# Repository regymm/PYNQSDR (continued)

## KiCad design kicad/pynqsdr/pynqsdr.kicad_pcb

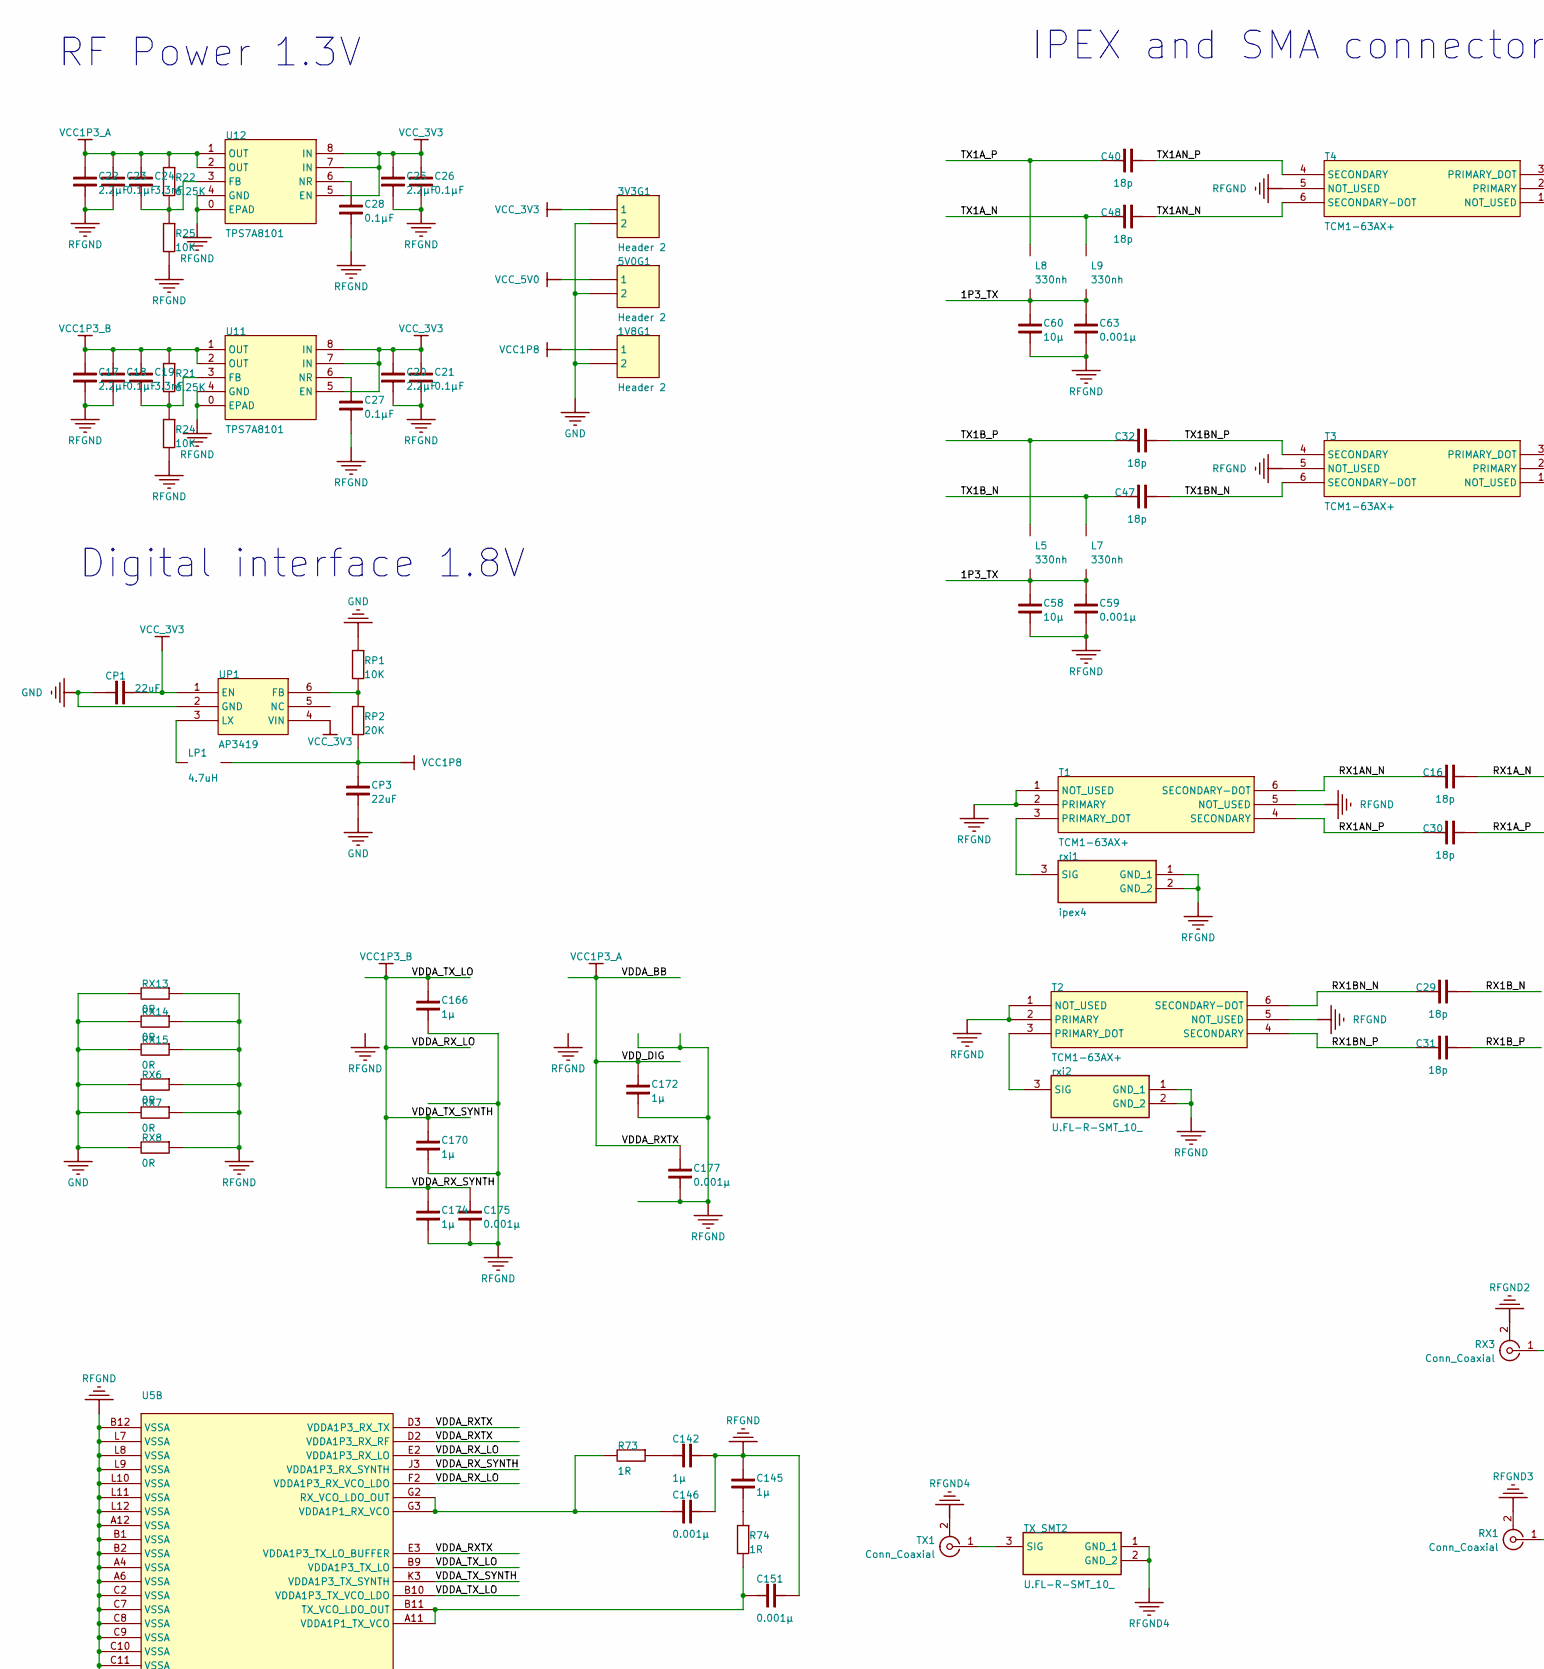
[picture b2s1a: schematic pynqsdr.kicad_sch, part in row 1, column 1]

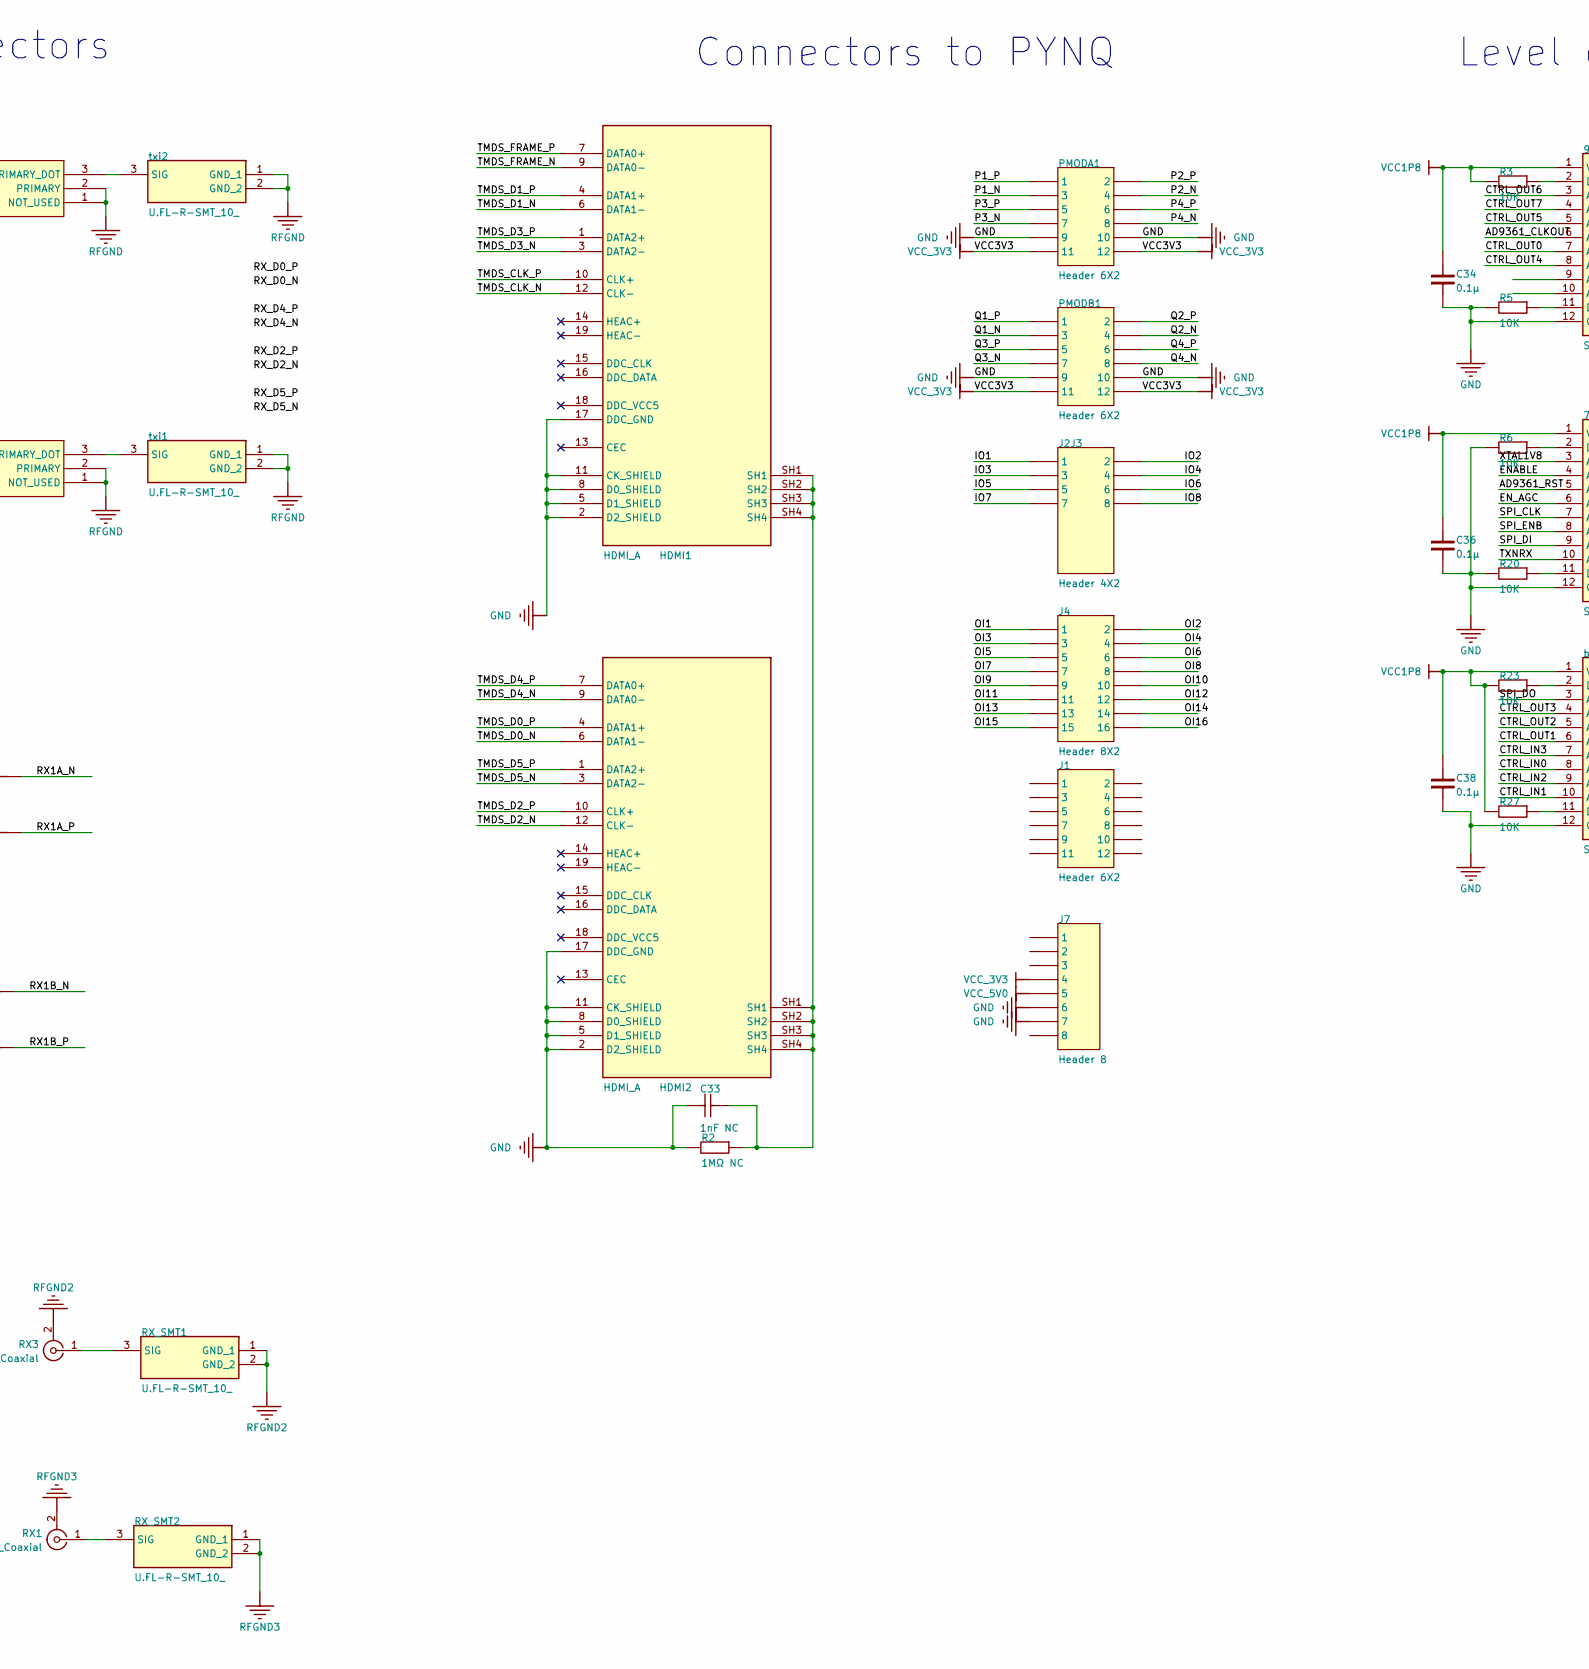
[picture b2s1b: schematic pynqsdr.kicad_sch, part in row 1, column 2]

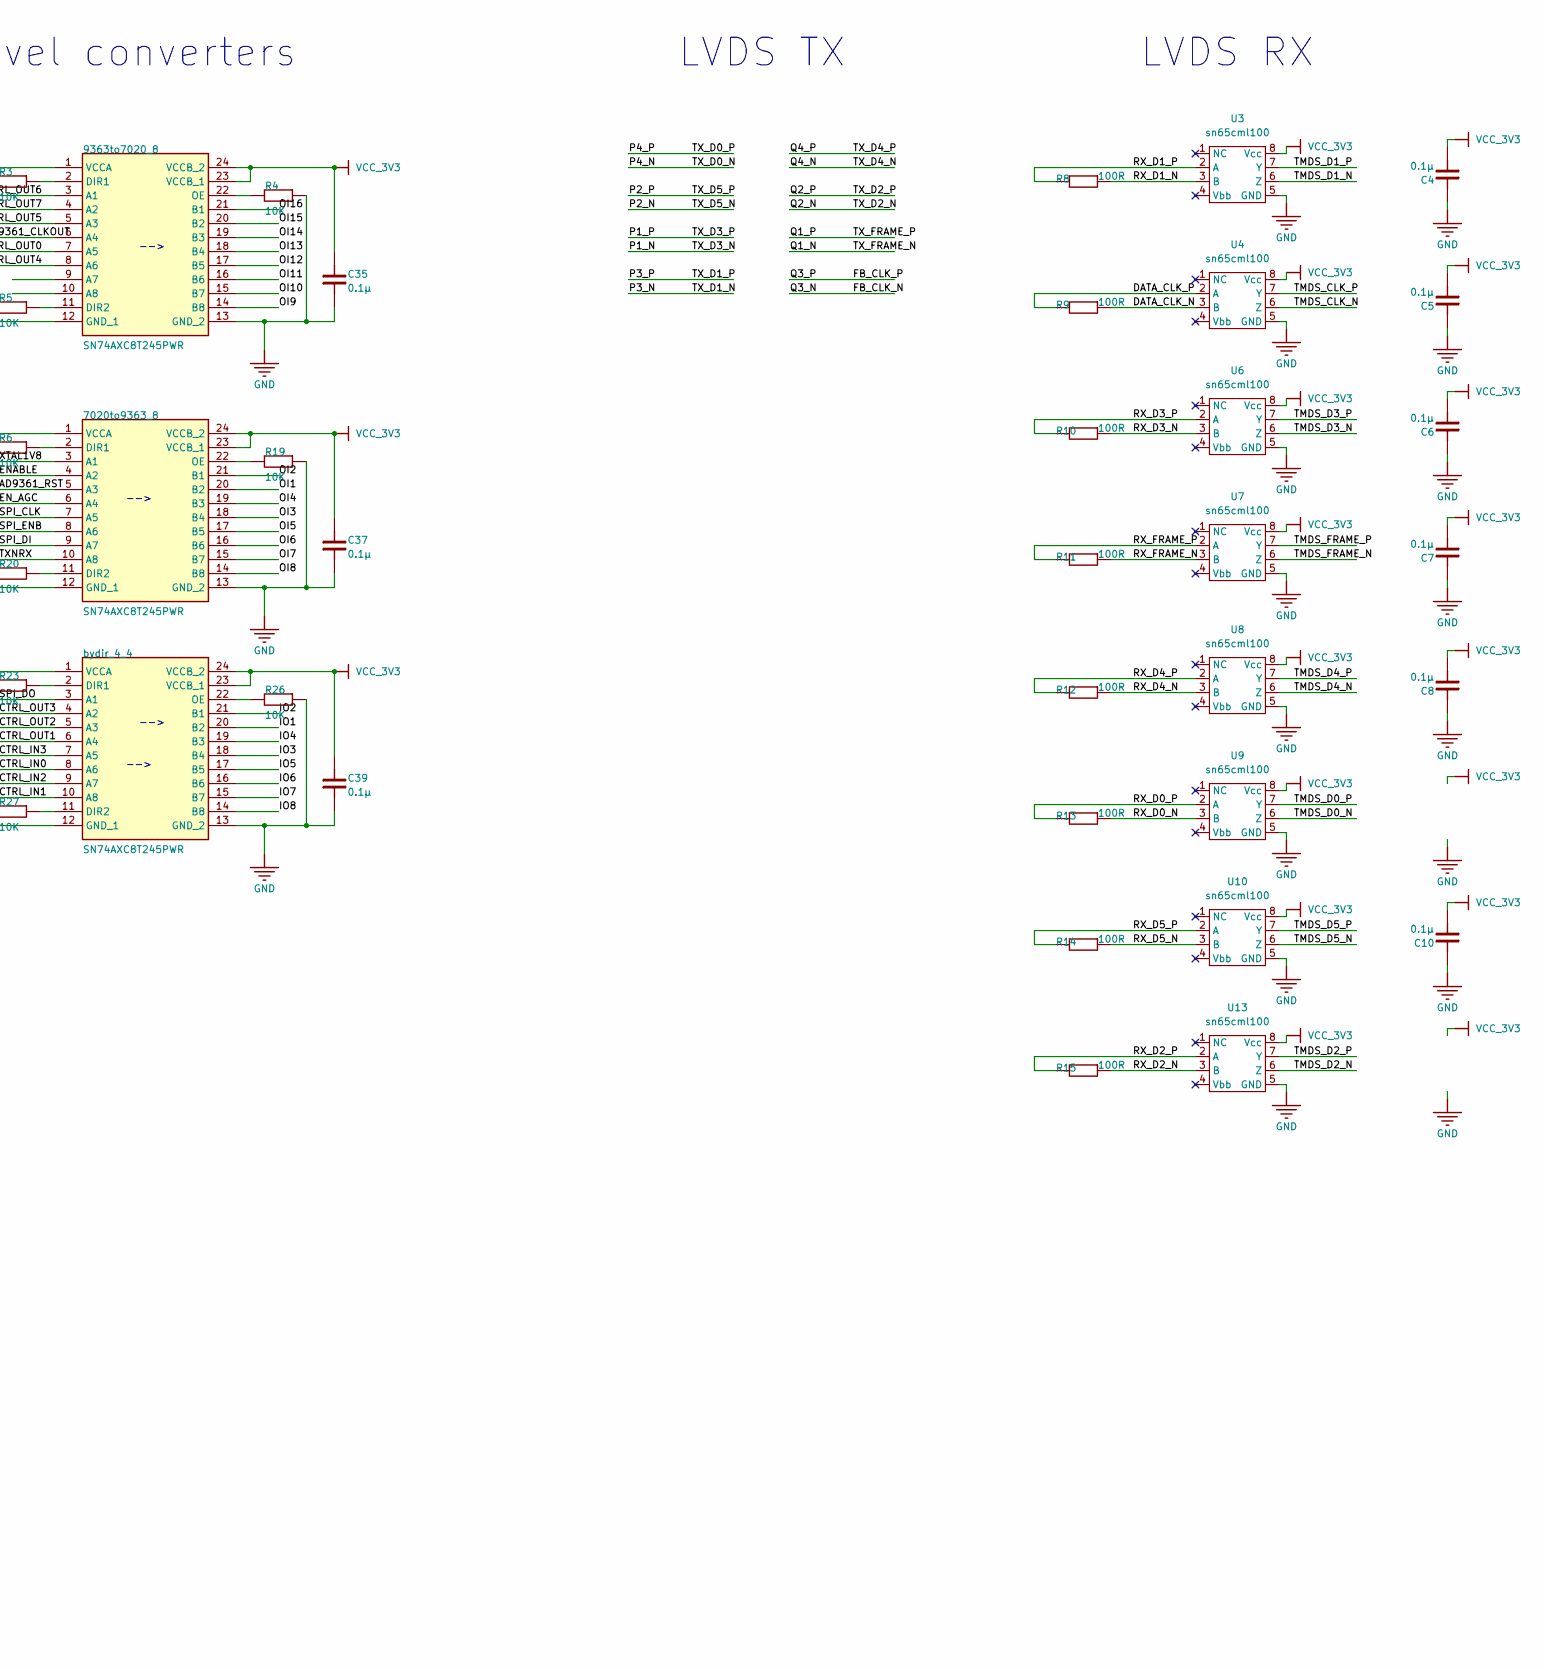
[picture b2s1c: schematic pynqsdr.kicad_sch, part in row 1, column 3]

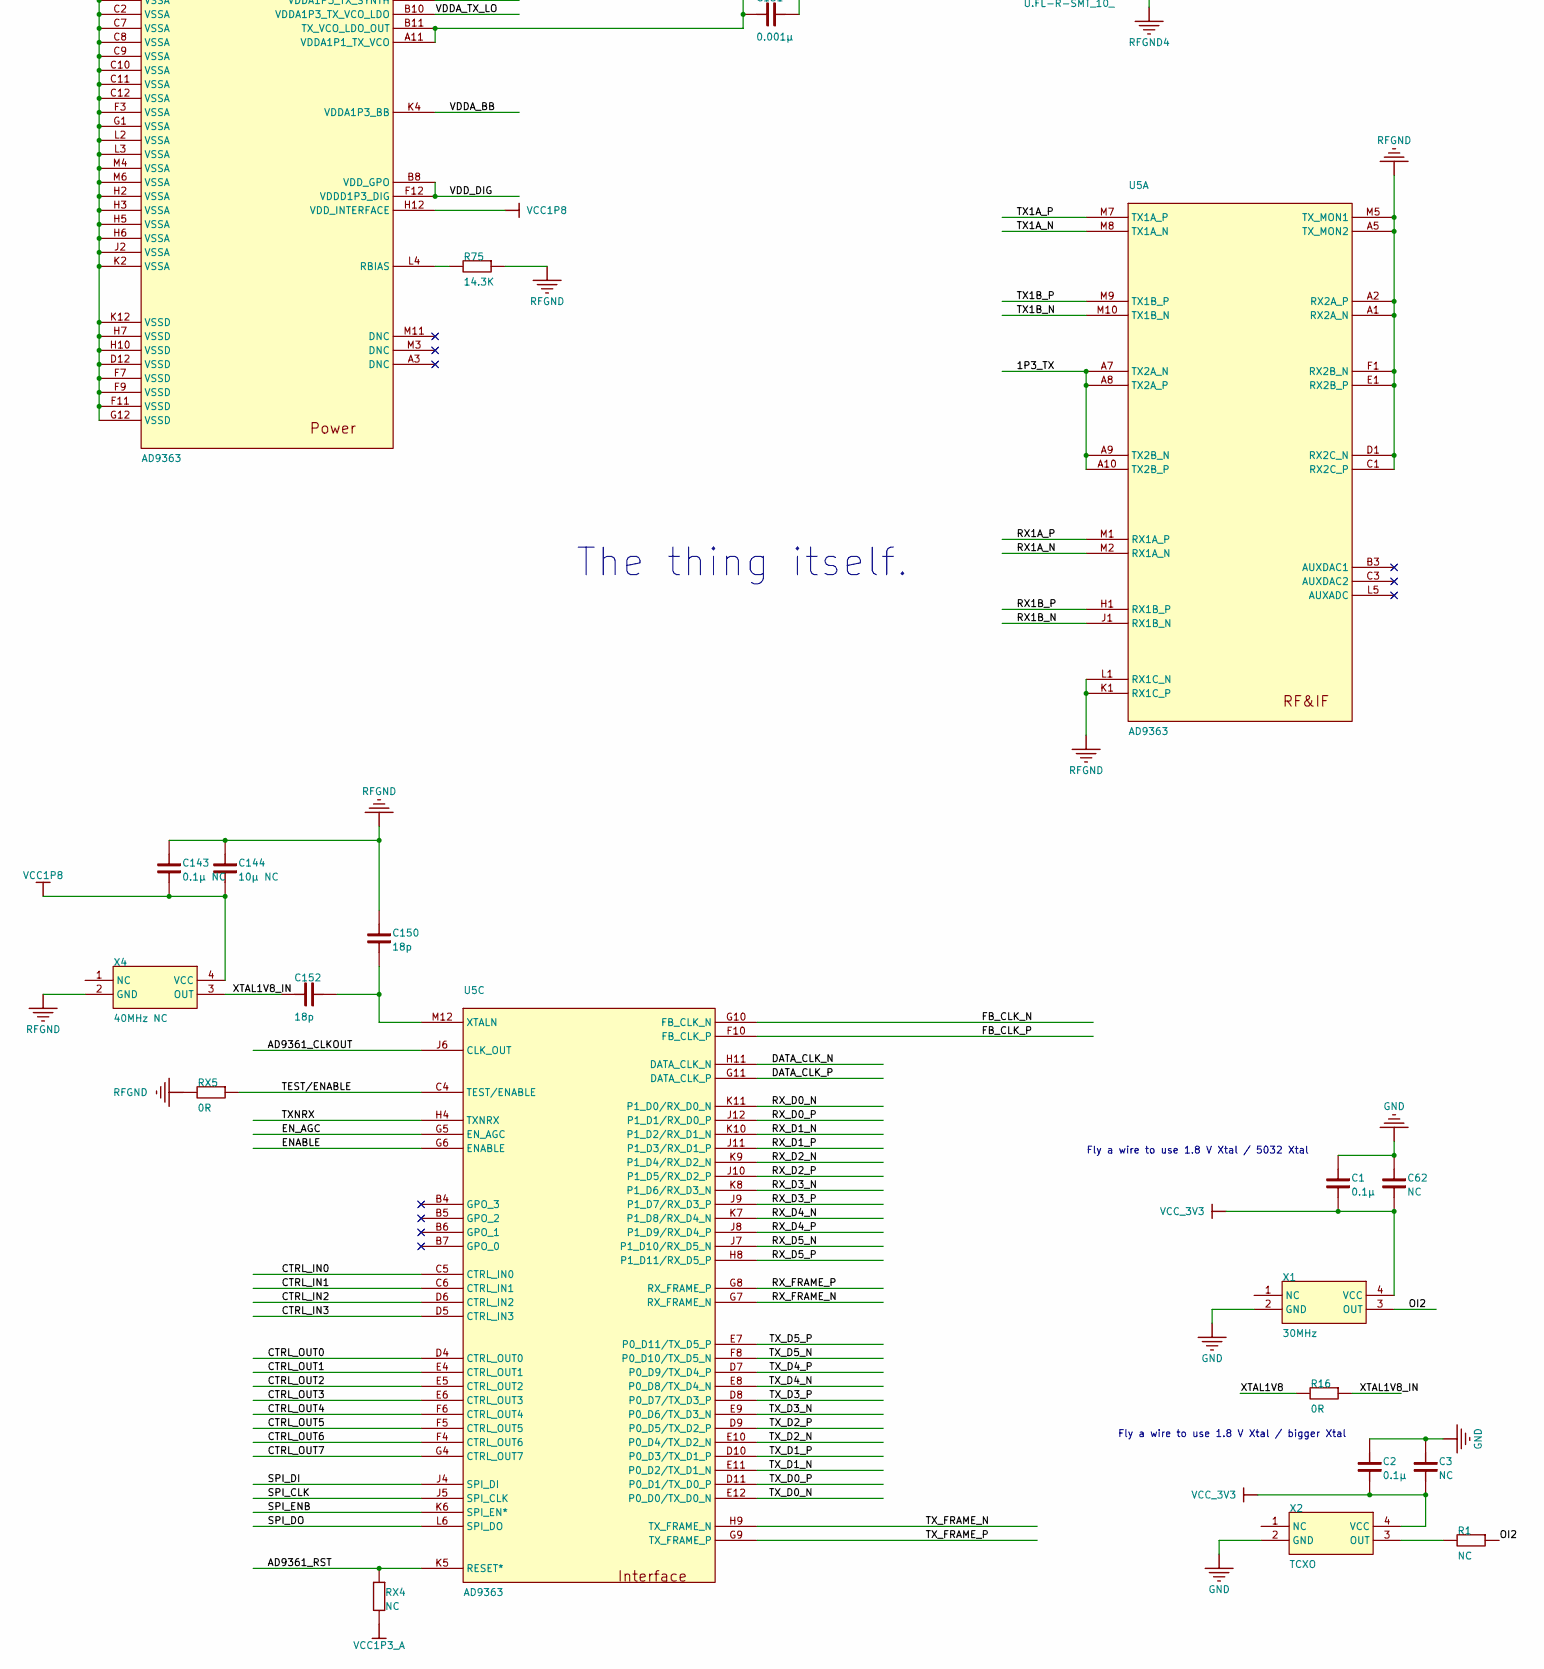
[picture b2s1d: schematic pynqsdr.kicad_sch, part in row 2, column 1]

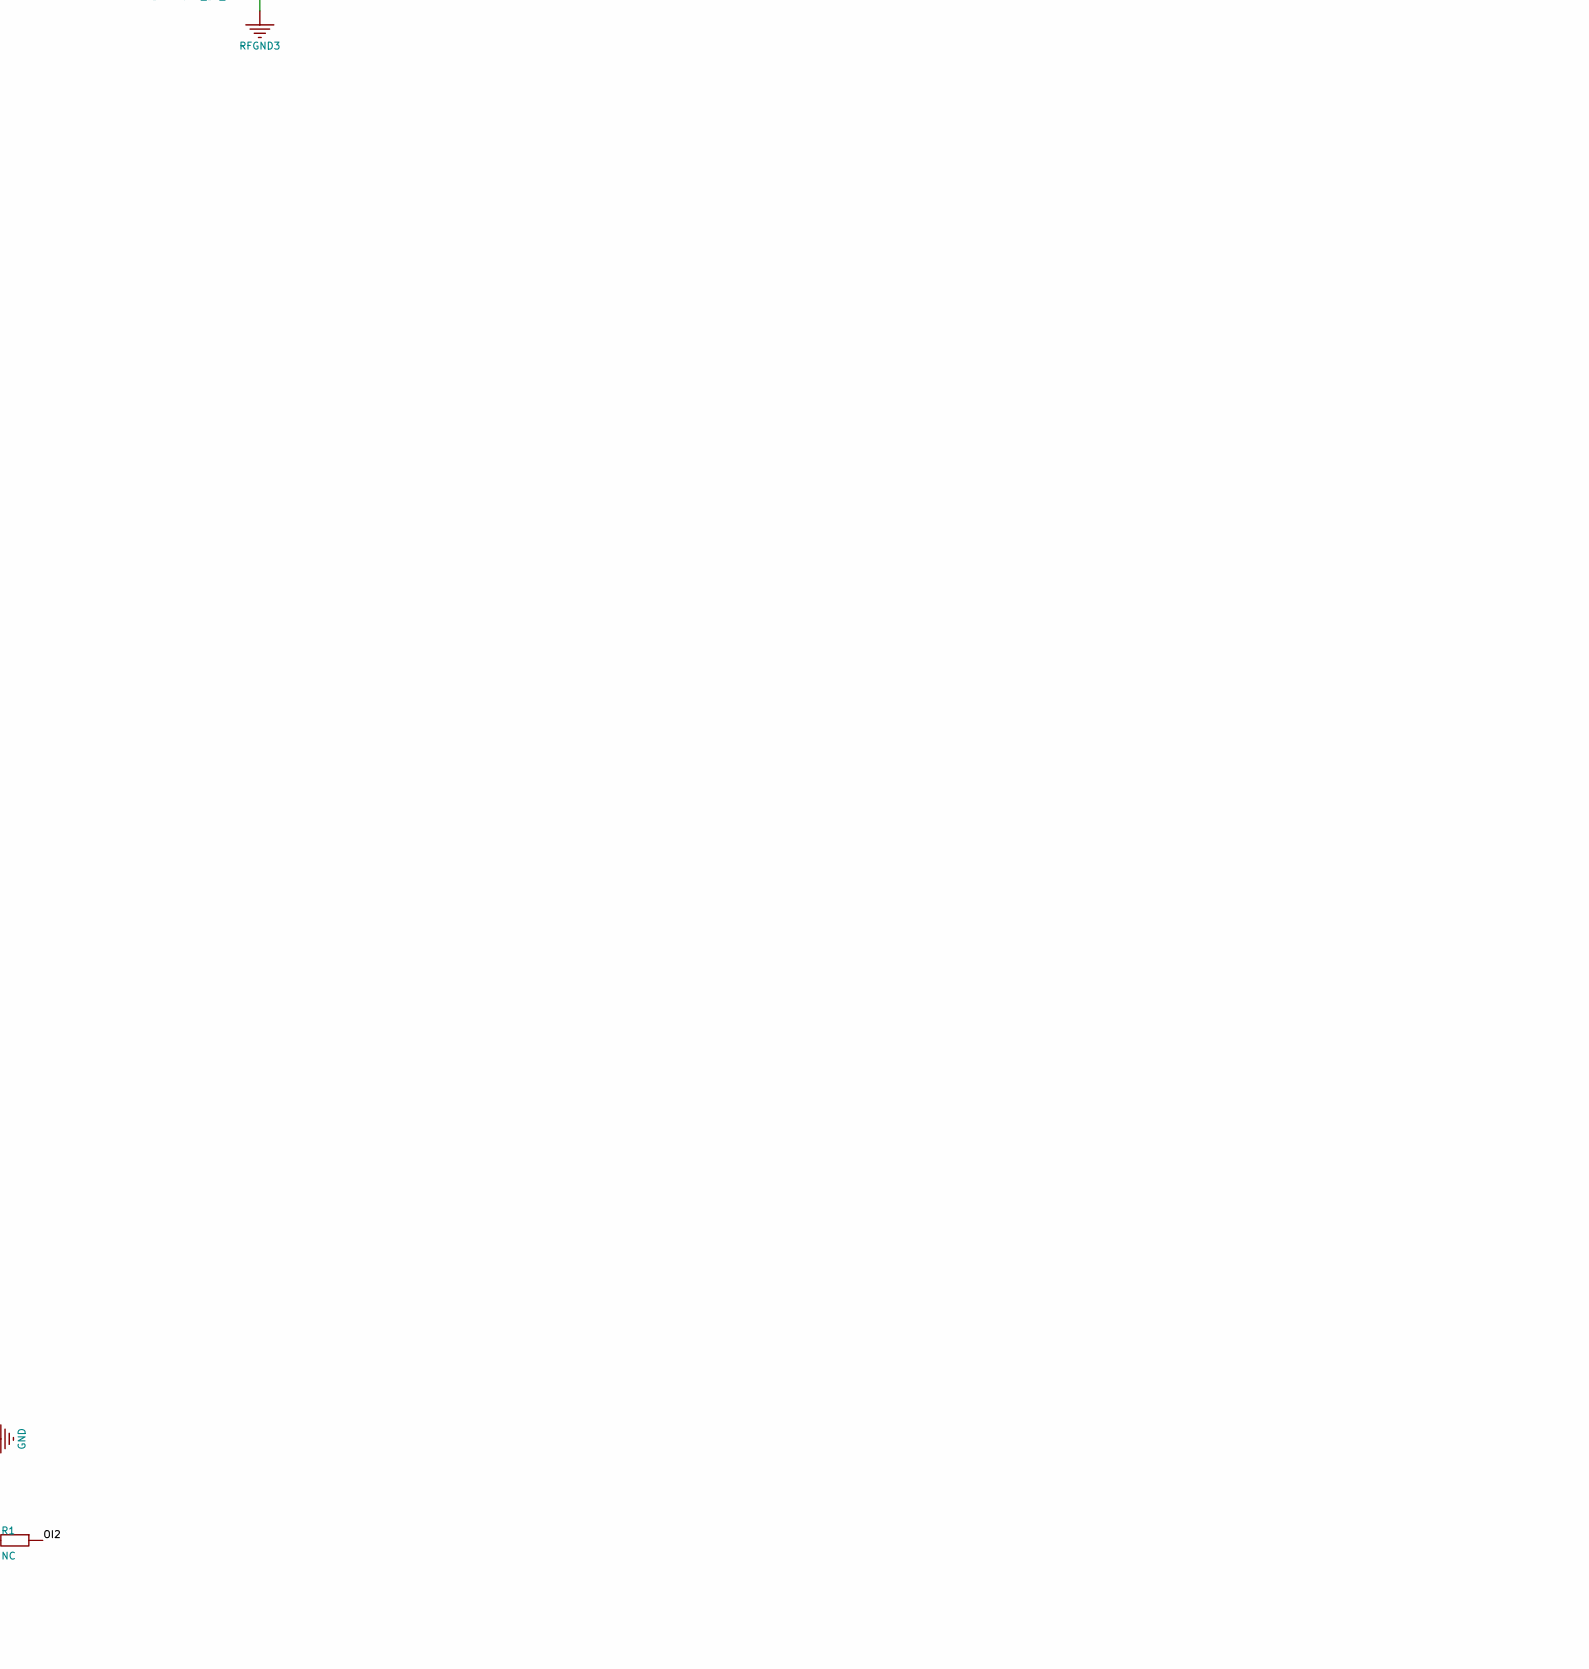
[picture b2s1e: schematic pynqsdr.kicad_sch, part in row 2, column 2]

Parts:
1V8G1, 3V3G1, 5V0G1: Header 2; HDR1X2
7020to9363_8, 9363to7020_8: SN74AXC8T245PWR; SOP65P640X120-24N; MANUFACTURER_PART_NUMBER SN74AXC8T245PWR; MOUSER PART NUMBER 595-SN74AXC8T245PWR
C1, C2, C4, C5, C6, C7, C8, C10, C34, C35, C36, C37, C38, C39: 0.1μ; LC-0402_C
C3, C62: NC; LC-0402_C
C16, C29, C30, C31, C32, C40, C47, C48, C150, C152: 18p; LC-0402_C
C17, C22: 2.2μF; LC-0805_C
C18, C23, C27, C28: 0.1μF; LC-0402_C
C19, C24: 3.3nF; LC-0402_C
C20, C25: 2.2μF; LC-0402_C
C21, C26: 0.1μF; LC-0805_C
C33: 1nF NC; 0805_C
C58, C60: 10μ; LC-0402_C
C59, C63, C146, C151, C175, C177: 0.001μ; LC-0402_C
C142, C145, C166, C170, C172, C174: 1μ; LC-0402_C
C143: 0.1μ NC; LC-0402_C
C144: 10μ NC; LC-0402_C
CP1, CP3: 22uF; LC-0805_C
HDMI1, HDMI2: HDMI_A
J1: Header 6X2; HDR2X6
J2J3: Header 4X2; HDR2X8
J4: Header 8X2; HDR2X8
J7: Header 8; HDR1X8
L5, L7, L8, L9: 330nh; LC-0603_L
LP1: 4.7uH; L1008
PMODA1: Header 6X2; HDR2X6
PMODB1: Header 6X2; HDR2X6
R1: NC; LC-0402_R
R2: 1MΩ NC; 0805_R
R3, R4, R5, R6, R19, R20, R23, R24, R25, R26, R27: 10K; LC-0402_R
R8, R9, R10, R11, R12, R13, R14, R15: 100R; LC-0402_R
R16: 0R; LC-0402_R
R21, R22: 6.25K; LC-0402_R
R73, R74: 1R; LC-0402_R
R75: 14.3K; LC-0402_R
RP1: 10K; LC-0402_R
RP2: 20K; LC-0402_R
RX1, RX3: Conn_Coaxial; SMA_Amphenol_132289_EdgeMount
RX4: NC; LC-0402_R
RX5: 0R; LC-0402_R
RX6, RX7, RX8, RX13, RX14, RX15: 0R; LC-0603_L
RX_SMT1, RX_SMT2: U.FL-R-SMT_10_; UFLRSMT10; MANUFACTURER_PART_NUMBER U.FL-R-SMT(10); MOUSER PART NUMBER 798-U.FL-R-SMT10
T1, T2, T3, T4: TCM1-63AX+; TSML150W160H160
TX1: Conn_Coaxial; SMA_Amphenol_132289_EdgeMount
TX_SMT2: U.FL-R-SMT_10_; UFLRSMT10; MANUFACTURER_PART_NUMBER U.FL-R-SMT(10); MOUSER PART NUMBER 798-U.FL-R-SMT10
U3, U4, U6, U7, U8, U9, U10, U13: sn65cml100; TSSOP-8_3x3mm_P0.65mm
U5: AD9363; AD936X
U11, U12: TPS7A8101
UP1: AP3419
X1: 30MHz; OSC-SMD_4P-L3.2-W2.5-BL
X2: TCXO; Crystal_SMD_7050-4Pin_7.0x5.0mm
X4: 40MHz NC; OSC-SMD_4P-L3.2-W2.5-BL
bydir_4_4: SN74AXC8T245PWR; SOP65P640X120-24N; MANUFACTURER_PART_NUMBER SN74AXC8T245PWR; MOUSER PART NUMBER 595-SN74AXC8T245PWR
rxi1: ipex4; UFLRSMT10; MANUFACTURER_PART_NUMBER U.FL-R-SMT(10); MOUSER PART NUMBER 798-U.FL-R-SMT10
rxi2: U.FL-R-SMT_10_; UFLRSMT10; MANUFACTURER_PART_NUMBER U.FL-R-SMT(10); MOUSER PART NUMBER 798-U.FL-R-SMT10
txi1, txi2: U.FL-R-SMT_10_; UFLRSMT10; MANUFACTURER_PART_NUMBER U.FL-R-SMT(10); MOUSER PART NUMBER 798-U.FL-R-SMT10

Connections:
/1P3_TX: C58.1, C59.2, C60.1, C63.2, L5.1, L7.1, L8.1, L9.1, U5.A7 (TX2A_N), U5.A8 (TX2A_P), U5.A9 (TX2B_N), U5.A10 (TX2B_P)
/AD9361_CLKOUT: 9363to7020_8.6 (A4), U5.J6 (CLK_OUT)
/AD9361_RST: 7020to9363_8.5 (A3), RX4.1, U5.K5 (RESET*)
/CTRL_IN0: U5.C5 (CTRL_IN0), bydir_4_4.8 (A6)
/CTRL_IN1: U5.C6 (CTRL_IN1), bydir_4_4.10 (A8)
/CTRL_IN2: U5.D6 (CTRL_IN2), bydir_4_4.9 (A7)
/CTRL_IN3: U5.D5 (CTRL_IN3), bydir_4_4.7 (A5)
/CTRL_OUT0: 9363to7020_8.7 (A5), U5.D4 (CTRL_OUT0)
/CTRL_OUT1: U5.E4 (CTRL_OUT1), bydir_4_4.6 (A4)
/CTRL_OUT2: U5.E5 (CTRL_OUT2), bydir_4_4.5 (A3)
/CTRL_OUT3: U5.E6 (CTRL_OUT3), bydir_4_4.4 (A2)
/CTRL_OUT4: 9363to7020_8.8 (A6), U5.F6 (CTRL_OUT4)
/CTRL_OUT5: 9363to7020_8.5 (A3), U5.F5 (CTRL_OUT5)
/CTRL_OUT6: 9363to7020_8.3 (A1), U5.F4 (CTRL_OUT6)
/CTRL_OUT7: 9363to7020_8.4 (A2), U5.G4 (CTRL_OUT7)
/DATA_CLK_N: R9.2, U4.3 (B), U5.H11 (DATA_CLK_N)
/DATA_CLK_P: R9.1, U4.2 (A), U5.G11 (DATA_CLK_P)
/ENABLE: 7020to9363_8.4 (A2), U5.G6 (ENABLE)
/EN_AGC: 7020to9363_8.6 (A4), U5.G5 (EN_AGC)
/FB_CLK_N: PMODB1.7, U5.G10 (FB_CLK_N)
/FB_CLK_P: PMODB1.5, U5.F10 (FB_CLK_P)
/IO1: J2J3.1, bydir_4_4.20 (B2)
/IO2: J2J3.2, bydir_4_4.21 (B1)
/IO3: J2J3.3, bydir_4_4.18 (B4)
/IO4: J2J3.4, bydir_4_4.19 (B3)
/IO5: J2J3.5, bydir_4_4.17 (B5)
/IO6: J2J3.6, bydir_4_4.16 (B6)
/IO7: J2J3.7, bydir_4_4.15 (B7)
/IO8: J2J3.8, bydir_4_4.14 (B8)
/OI1: 7020to9363_8.20 (B2), J4.1
/OI2: 7020to9363_8.21 (B1), J4.2, R1.1, X1.3 (OUT)
/OI3: 7020to9363_8.18 (B4), J4.3
/OI4: 7020to9363_8.19 (B3), J4.4
/OI5: 7020to9363_8.17 (B5), J4.5
/OI6: 7020to9363_8.16 (B6), J4.6
/OI7: 7020to9363_8.15 (B7), J4.7
/OI8: 7020to9363_8.14 (B8), J4.8
/OI9: 9363to7020_8.14 (B8), J4.9
/OI10: 9363to7020_8.15 (B7), J4.10
/OI11: 9363to7020_8.16 (B6), J4.11
/OI12: 9363to7020_8.17 (B5), J4.12
/OI13: 9363to7020_8.18 (B4), J4.13
/OI14: 9363to7020_8.19 (B3), J4.14
/OI15: 9363to7020_8.20 (B2), J4.15
/OI16: 9363to7020_8.21 (B1), J4.16
/P1_N: PMODA1.3, U5.E9 (P0_D6/TX_D3_N)
/P1_P: PMODA1.1, U5.D8 (P0_D7/TX_D3_P)
/P2_N: PMODA1.4, U5.F8 (P0_D10/TX_D5_N)
/P2_P: PMODA1.2, U5.E7 (P0_D11/TX_D5_P)
/P3_N: PMODA1.7, U5.E11 (P0_D2/TX_D1_N)
/P3_P: PMODA1.5, U5.D10 (P0_D3/TX_D1_P)
/P4_N: PMODA1.8, U5.E12 (P0_D0/TX_D0_N)
/P4_P: PMODA1.6, U5.D11 (P0_D1/TX_D0_P)
/Q1_N: PMODB1.3, U5.H9 (TX_FRAME_N)
/Q1_P: PMODB1.1, U5.G9 (TX_FRAME_P)
/Q2_N: PMODB1.4, U5.E10 (P0_D4/TX_D2_N)
/Q2_P: PMODB1.2, U5.D9 (P0_D5/TX_D2_P)
/Q4_N: PMODB1.8, U5.E8 (P0_D8/TX_D4_N)
/Q4_P: PMODB1.6, U5.D7 (P0_D9/TX_D4_P)
/RX1AN_N: C16.1, T1.6 (SECONDARY-DOT)
/RX1AN_P: C30.1, T1.4 (SECONDARY)
/RX1A_N: C16.2, U5.M2 (RX1A_N)
/RX1A_P: C30.2, U5.M1 (RX1A_P)
/RX1BN_N: C29.1, T2.6 (SECONDARY-DOT)
/RX1BN_P: C31.1, T2.4 (SECONDARY)
/RX1B_N: C29.2, U5.J1 (RX1B_N)
/RX1B_P: C31.2, U5.H1 (RX1B_P)
/RX_D0_N: R13.2, U5.K11 (P1_D0/RX_D0_N), U9.3 (B)
/RX_D0_P: R13.1, U5.J12 (P1_D1/RX_D0_P), U9.2 (A)
/RX_D1_N: R8.2, U3.3 (B), U5.K10 (P1_D2/RX_D1_N)
/RX_D1_P: R8.1, U3.2 (A), U5.J11 (P1_D3/RX_D1_P)
/RX_D2_N: R15.2, U5.K9 (P1_D4/RX_D2_N), U13.3 (B)
/RX_D2_P: R15.1, U5.J10 (P1_D5/RX_D2_P), U13.2 (A)
/RX_D3_N: R10.2, U5.K8 (P1_D6/RX_D3_N), U6.3 (B)
/RX_D3_P: R10.1, U5.J9 (P1_D7/RX_D3_P), U6.2 (A)
/RX_D4_N: R12.2, U5.K7 (P1_D8/RX_D4_N), U8.3 (B)
/RX_D4_P: R12.1, U5.J8 (P1_D9/RX_D4_P), U8.2 (A)
/RX_D5_N: R14.2, U5.J7 (P1_D10/RX_D5_N), U10.3 (B)
/RX_D5_P: R14.1, U5.H8 (P1_D11/RX_D5_P), U10.2 (A)
/RX_FRAME_N: R11.2, U5.G7 (RX_FRAME_N), U7.3 (B)
/RX_FRAME_P: R11.1, U5.G8 (RX_FRAME_P), U7.2 (A)
/SPI_CLK: 7020to9363_8.7 (A5), U5.J5 (SPI_CLK)
/SPI_DI: 7020to9363_8.9 (A7), U5.J4 (SPI_DI)
/SPI_DO: U5.L6 (SPI_DO), bydir_4_4.3 (A1)
/SPI_ENB: 7020to9363_8.8 (A6), U5.K6 (SPI_EN*)
/TEST/ENABLE: RX5.2, U5.C4 (TEST/ENABLE)
/TMDS_CLK_N: HDMI1.12 (CLK-), U4.6 (Z)
/TMDS_CLK_P: HDMI1.10 (CLK+), U4.7 (Y)
/TMDS_D0_N: HDMI2.6 (DATA1-), U9.6 (Z)
/TMDS_D0_P: HDMI2.4 (DATA1+), U9.7 (Y)
/TMDS_D1_N: HDMI1.6 (DATA1-), U3.6 (Z)
/TMDS_D1_P: HDMI1.4 (DATA1+), U3.7 (Y)
/TMDS_D2_N: HDMI2.12 (CLK-), U13.6 (Z)
/TMDS_D2_P: HDMI2.10 (CLK+), U13.7 (Y)
/TMDS_D3_N: HDMI1.3 (DATA2-), U6.6 (Z)
/TMDS_D3_P: HDMI1.1 (DATA2+), U6.7 (Y)
/TMDS_D4_N: HDMI2.9 (DATA0-), U8.6 (Z)
/TMDS_D4_P: HDMI2.7 (DATA0+), U8.7 (Y)
/TMDS_D5_N: HDMI2.3 (DATA2-), U10.6 (Z)
/TMDS_D5_P: HDMI2.1 (DATA2+), U10.7 (Y)
/TMDS_FRAME_N: HDMI1.9 (DATA0-), U7.6 (Z)
/TMDS_FRAME_P: HDMI1.7 (DATA0+), U7.7 (Y)
/TX1AN_N: C48.2, T4.6 (SECONDARY-DOT)
/TX1AN_P: C40.2, T4.4 (SECONDARY)
/TX1A_N: C48.1, L9.2, U5.M8 (TX1A_N)
/TX1A_P: C40.1, L8.2, U5.M7 (TX1A_P)
/TX1BN_N: C47.2, T3.6 (SECONDARY-DOT)
/TX1BN_P: C32.2, T3.4 (SECONDARY)
/TX1B_N: C47.1, L7.2, U5.M10 (TX1B_N)
/TX1B_P: C32.1, L5.2, U5.M9 (TX1B_P)
/TXNRX: 7020to9363_8.10 (A8), U5.H4 (TXNRX)
/XTAL1V8: 7020to9363_8.3 (A1), R16.2
/XTAL1V8_IN: C152.2, R16.1, X4.3 (OUT)
GND: 1V8G1.2, 3V3G1.2, 5V0G1.2, 7020to9363_8.12 (GND_1), 7020to9363_8.13 (GND_2), 9363to7020_8.12 (GND_1), 9363to7020_8.13 (GND_2), C1.1, C2.1, C3.1, C4.2, C5.2, C6.2, C7.2, C8.2, C10.2, C33.2, C34.1, C35.1, C36.1, C37.1, C38.1, C39.1, C62.1, CP1.1, CP3.1, HDMI1.2 (D2_SHIELD), HDMI1.5 (D1_SHIELD), HDMI1.8 (D0_SHIELD), HDMI1.11 (CK_SHIELD), HDMI1.17 (DDC_GND), HDMI2.2 (D2_SHIELD), HDMI2.5 (D1_SHIELD), HDMI2.8 (D0_SHIELD), HDMI2.11 (CK_SHIELD), HDMI2.17 (DDC_GND), J7.6, J7.7, PMODA1.9, PMODA1.10, PMODB1.9, PMODB1.10, R2.2, R4.1, R5.2, R6.2, R19.1, R20.2, R26.1, RP1.2, RX6.2, RX7.2, RX8.2, RX13.2, RX14.2, RX15.2, U3.5 (GND), U4.5 (GND), U6.5 (GND), U7.5 (GND), U8.5 (GND), U9.5 (GND), U10.5 (GND), U13.5 (GND), UP1.2 (GND), X1.2 (GND), X2.2 (GND), bydir_4_4.12 (GND_1), bydir_4_4.13 (GND_2)
unnamed: 7020to9363_8.2 (DIR1), R6.1
unnamed: 7020to9363_8.11 (DIR2), R20.1
unnamed: 7020to9363_8.22 (OE), R19.2
unnamed: 9363to7020_8.2 (DIR1), R3.1
unnamed: 9363to7020_8.11 (DIR2), R5.1
unnamed: 9363to7020_8.22 (OE), R4.2
unnamed: C19.1, R21.2, R24.1, U11.3 (FB)
unnamed: C24.1, R22.2, R25.1, U12.3 (FB)
unnamed: C27.2, U11.6 (NR)
unnamed: C28.2, U12.6 (NR)
unnamed: C33.1, HDMI1.SH1, HDMI1.SH2, HDMI1.SH3, HDMI1.SH4, HDMI2.SH1, HDMI2.SH2, HDMI2.SH3, HDMI2.SH4, R2.1
unnamed: C142.1, R73.2
unnamed: C145.2, R74.1
unnamed: C146.2, R73.1, U5.G2 (RX_VCO_LDO_OUT), U5.G3 (VDDA1P1_RX_VCO)
unnamed: C150.2, C152.1, U5.M12 (XTALN)
unnamed: C151.2, R74.2, U5.A11 (VDDA1P1_TX_VCO), U5.B11 (TX_VCO_LDO_OUT)
unnamed: LP1.1, UP1.3 (LX)
unnamed: R1.2, X2.3 (OUT)
unnamed: R23.1, bydir_4_4.2 (DIR1)
unnamed: R26.2, bydir_4_4.22 (OE)
unnamed: R27.1, bydir_4_4.11 (DIR2)
unnamed: R75.1, U5.L4 (RBIAS)
unnamed: RP1.1, RP2.2, UP1.6 (FB)
unnamed: RX1.1 (In), RX_SMT2.3 (SIG)
unnamed: RX3.1 (In), RX_SMT1.3 (SIG)
unnamed: T1.3 (PRIMARY_DOT), rxi1.3 (SIG)
unnamed: T2.3 (PRIMARY_DOT), rxi2.3 (SIG)
unnamed: T3.3 (PRIMARY_DOT), txi1.3 (SIG)
unnamed: T4.3 (PRIMARY_DOT), txi2.3 (SIG)
unnamed: TX1.1 (In), TX_SMT2.3 (SIG)
RFGND: C17.1, C18.1, C20.1, C21.1, C22.1, C23.1, C25.1, C26.1, C27.1, C28.1, C58.2, C59.1, C60.2, C63.1, C142.2, C143.1, C144.1, C145.1, C146.1, C150.1, C151.1, C166.2, C170.2, C172.2, C174.2, C175.2, C177.2, R24.2, R25.2, R75.2, RX5.1, RX6.1, RX7.1, RX8.1, RX13.1, RX14.1, RX15.1, T1.1 (NOT_USED), T1.2 (PRIMARY), T1.5 (NOT_USED), T2.1 (NOT_USED), T2.2 (PRIMARY), T2.5 (NOT_USED), T3.1 (NOT_USED), T3.2 (PRIMARY), T3.5 (NOT_USED), T4.1 (NOT_USED), T4.2 (PRIMARY), T4.5 (NOT_USED), U5.A1 (RX2A_N), U5.A2 (RX2A_P), U5.A4 (VSSA), U5.A5 (TX_MON2), U5.A6 (VSSA), U5.A12 (VSSA), U5.B1 (VSSA), U5.B2 (VSSA), U5.B12 (VSSA), U5.C1 (RX2C_P), U5.C2 (VSSA), U5.C7 (VSSA), U5.C8 (VSSA), U5.C9 (VSSA), U5.C10 (VSSA), U5.C11 (VSSA), U5.C12 (VSSA), U5.D1 (RX2C_N), U5.D12 (VSSD), U5.E1 (RX2B_P), U5.F1 (RX2B_N), U5.F3 (VSSA), U5.F7 (VSSD), U5.F9 (VSSD), U5.F11 (VSSD), U5.G1 (VSSA), U5.G12 (VSSD), U5.H2 (VSSA), U5.H3 (VSSA), U5.H5 (VSSA), U5.H6 (VSSA), U5.H7 (VSSD), U5.H10 (VSSD), U5.J2 (VSSA), U5.K1 (RX1C_P), U5.K2 (VSSA), U5.K12 (VSSD), U5.L1 (RX1C_N), U5.L2 (VSSA), U5.L3 (VSSA), U5.L7 (VSSA), U5.L8 (VSSA), U5.L9 (VSSA), U5.L10 (VSSA), U5.L11 (VSSA), U5.L12 (VSSA), U5.M4 (VSSA), U5.M5 (TX_MON1), U5.M6 (VSSA), U11.0 (EPAD), U11.4 (GND), U12.0 (EPAD), U12.4 (GND), X4.2 (GND), rxi1.1 (GND_1), rxi1.2 (GND_2), rxi2.1 (GND_1), rxi2.2 (GND_2), txi1.1 (GND_1), txi1.2 (GND_2), txi2.1 (GND_1), txi2.2 (GND_2)
RFGND2: RX3.2 (Ext), RX_SMT1.1 (GND_1), RX_SMT1.2 (GND_2)
RFGND3: RX1.2 (Ext), RX_SMT2.1 (GND_1), RX_SMT2.2 (GND_2)
RFGND4: TX1.2 (Ext), TX_SMT2.1 (GND_1), TX_SMT2.2 (GND_2)
VCC1P3_A: C22.2, C23.2, C24.2, C172.1, C177.1, R22.1, RX4.2, U5.B8 (VDD_GPO), U5.D2 (VDDA1P3_RX_RF), U5.D3 (VDDA1P3_RX_TX), U5.E3 (VDDA1P3_TX_LO_BUFFER), U5.F12 (VDDD1P3_DIG), U5.K4 (VDDA1P3_BB), U12.1 (OUT), U12.2 (OUT)
VCC1P3_B: C17.2, C18.2, C19.2, C166.1, C170.1, C174.1, C175.1, R21.1, U5.B9 (VDDA1P3_TX_LO), U5.B10 (VDDA1P3_TX_VCO_LDO), U5.E2 (VDDA1P3_RX_LO), U5.F2 (VDDA1P3_RX_VCO_LDO), U5.J3 (VDDA1P3_RX_SYNTH), U5.K3 (VDDA1P3_TX_SYNTH), U11.1 (OUT), U11.2 (OUT)
VCC1P8: 1V8G1.1, 7020to9363_8.1 (VCCA), 9363to7020_8.1 (VCCA), C34.2, C36.2, C38.2, C143.2, C144.2, CP3.2, LP1.2, R3.2, R23.2, R27.2, RP2.1, U5.H12 (VDD_INTERFACE), X4.4 (VCC), bydir_4_4.1 (VCCA)
VCC_3V3: 3V3G1.1, 7020to9363_8.23 (VCCB_1), 7020to9363_8.24 (VCCB_2), 9363to7020_8.23 (VCCB_1), 9363to7020_8.24 (VCCB_2), C1.2, C2.2, C3.2, C4.1, C5.1, C6.1, C7.1, C8.1, C10.1, C20.2, C21.2, C25.2, C26.2, C35.2, C37.2, C39.2, C62.2, CP1.2, J7.4, PMODA1.11, PMODA1.12, PMODB1.11, PMODB1.12, U3.8 (Vcc), U4.8 (Vcc), U6.8 (Vcc), U7.8 (Vcc), U8.8 (Vcc), U9.8 (Vcc), U10.8 (Vcc), U11.5 (EN), U11.7 (IN), U11.8 (IN), U12.5 (EN), U12.7 (IN), U12.8 (IN), U13.8 (Vcc), UP1.1 (EN), UP1.4 (VIN), X1.4 (VCC), X2.4 (VCC), bydir_4_4.23 (VCCB_1), bydir_4_4.24 (VCCB_2)
VCC_5V0: 5V0G1.1, J7.5

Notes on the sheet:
Digital interface 1.8V
IPEX and SMA connectors
Fly a wire to use 1.8 V Xtal / 5032 Xtal
LVDS RX
Level converters
Fly a wire to use 1.8 V Xtal / bigger Xtal
-->
The thing itself.
LVDS TX
RF Power 1.3V
Connectors to PYNQ

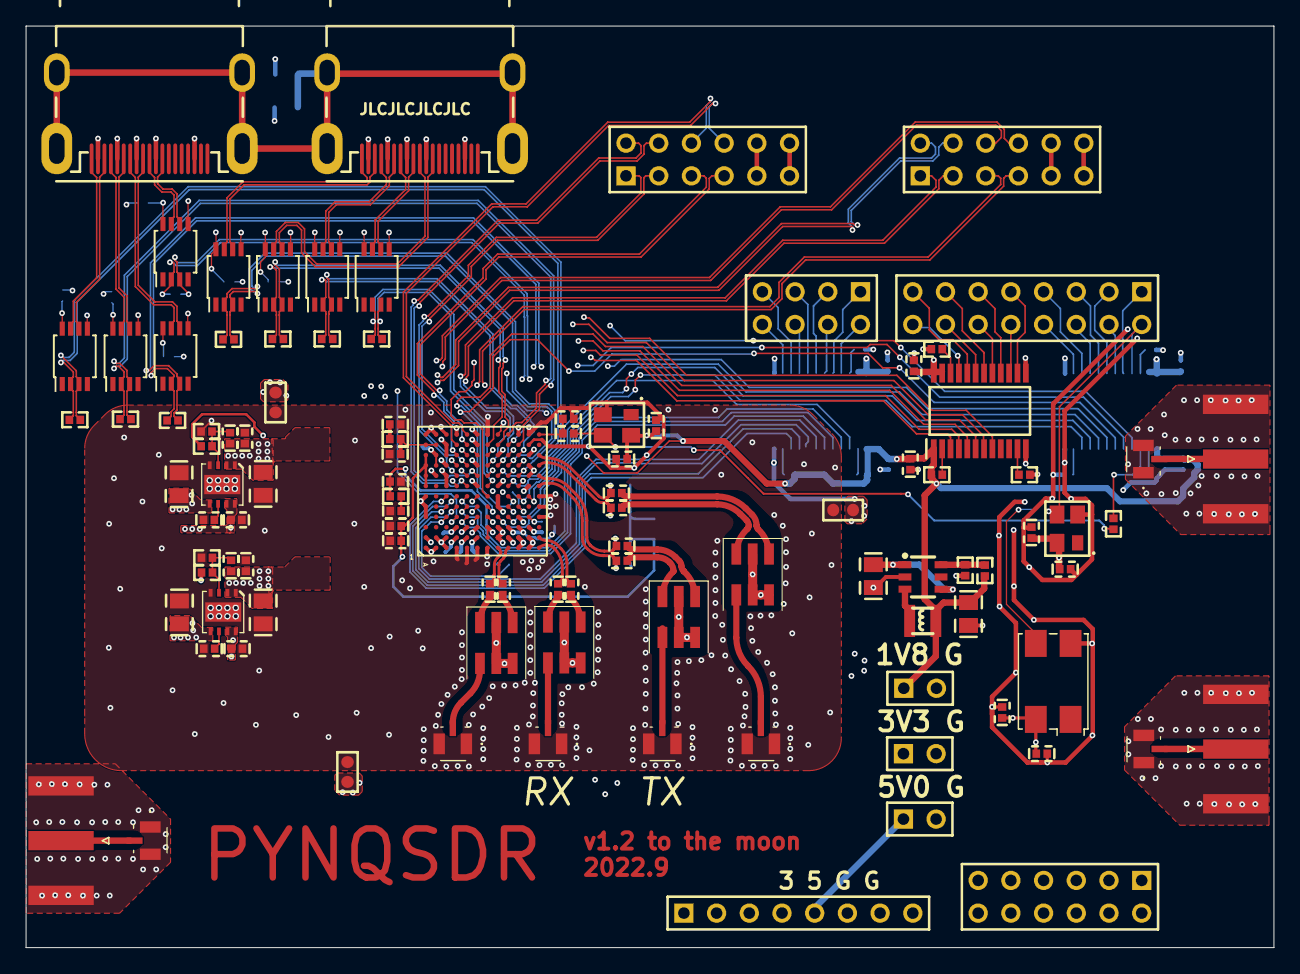
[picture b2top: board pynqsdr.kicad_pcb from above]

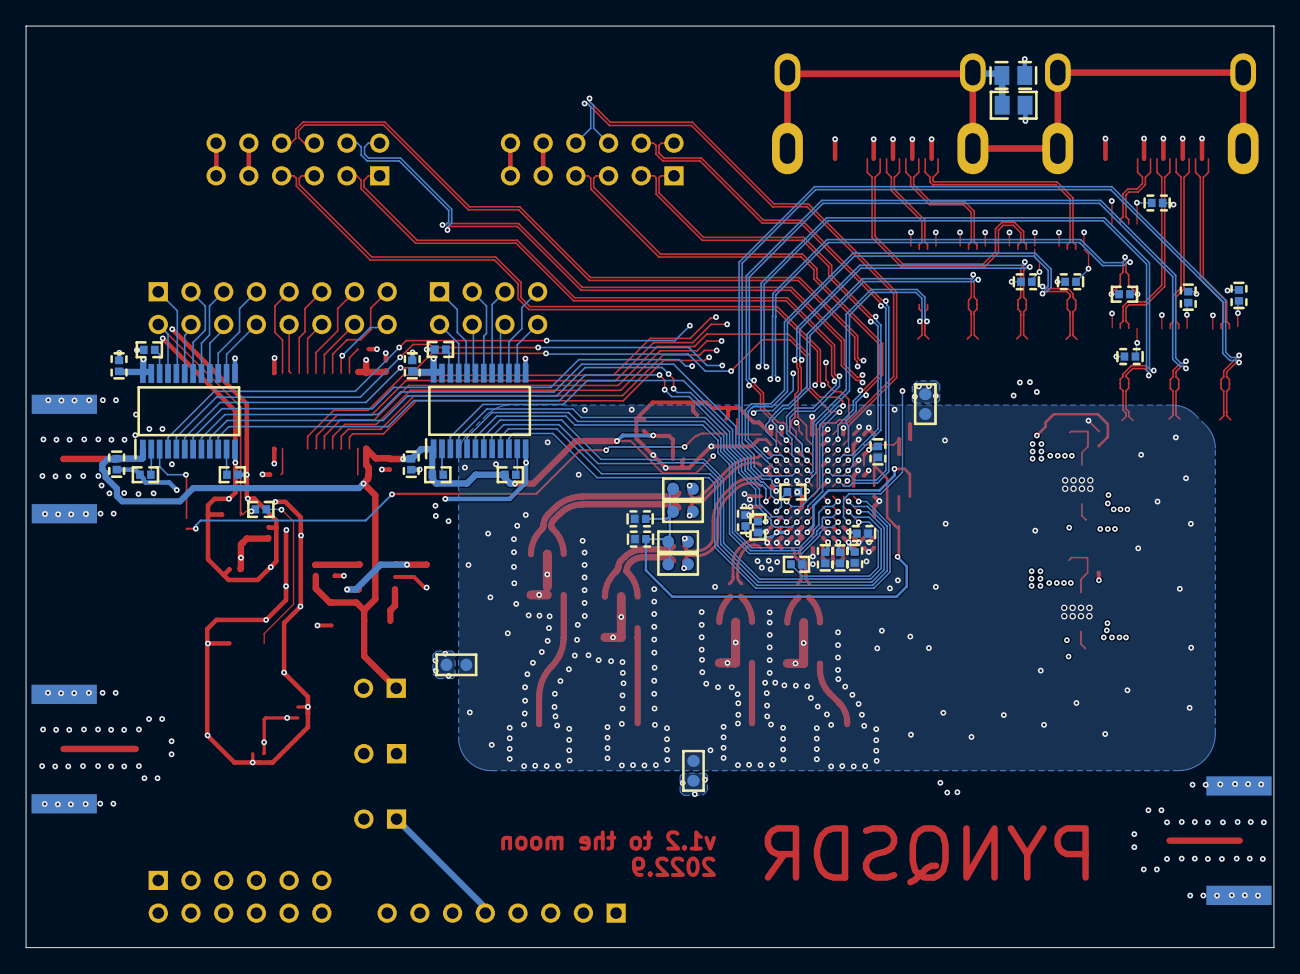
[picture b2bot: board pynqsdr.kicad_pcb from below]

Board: 4 copper layers, 96.9 x 71.6 mm, 142 parts (40 on the bottom side), 153 nets.
